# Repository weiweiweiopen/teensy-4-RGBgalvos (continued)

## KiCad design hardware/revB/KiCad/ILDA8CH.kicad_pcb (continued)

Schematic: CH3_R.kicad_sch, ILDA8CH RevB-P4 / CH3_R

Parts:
C161, C162: 4.7n; Capacitor_SMD__C_0603_1608Metric; MPN GRM1885C1H472JA01D; LCSC C85980
C163, C164: 100n; Capacitor_SMD__C_0603_1608Metric; MPN GRM188R71H104KA93D; LCSC C77055
C165, C166: 4.7u; Capacitor_SMD__C_0805_2012Metric; MPN GRM21BR61E475KA12L; LCSC C77077
R161, R162: 1k; Resistor_SMD__R_0603_1608Metric; MPN RT0603BRD071KL; LCSC C110776
R163, R164, R165, R166: 20k; Resistor_SMD__R_0603_1608Metric; MPN RT0603BRD0720KL; LCSC C723637
R167, R168: 10k; Resistor_SMD__R_0603_1608Metric; MPN RT0603BRD0710KL; LCSC C95204
R169, R170: 100k; Resistor_SMD__R_0603_1608Metric; MPN RC0603FR-07100KL; LCSC C14675
R405, R406: 10M; Resistor_SMD__R_0603_1608Metric; MPN RC0603FR-0710ML; LCSC C114606
U13: OPA4197IDR; Package_SO__SOIC-14_3.9x8.7mm_P1.27mm; MPN OPA4197IDR; LCSC C2058532

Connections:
+15A: C163.1, C165.1, U13.4 (V+); also elsewhere on the board
-15A: C164.2, C166.2, U13.11 (V-); also elsewhere on the board
B3N: R162.1, U13.6 (-), U13.7 (OUT)
B3P: R161.1, U13.1 (OUT), U13.2 (-)
F3N: C162.1, R162.2, R165.1
F3P: C161.1, R161.2, R163.1
GND: C161.2, C162.2, C163.2, C164.1, C165.2, C166.1, R164.2, R405.2, R406.2, U13.12 (+); also elsewhere on the board
IN3N: R170.2, R406.1, U13.5 (+)
IN3P: R169.2, R405.1, U13.3 (+)
INV3: R167.2, R168.2, U13.13 (-)
ISO_DAC3_N: R170.1; also elsewhere on the board
ISO_DAC3_P: R169.1; also elsewhere on the board
R_DRV_N: R168.1, U13.14 (OUT); also elsewhere on the board
R_DRV_P: R166.1, R167.1, U13.8 (OUT); also elsewhere on the board
SUM3N: R165.2, R166.2, U13.9 (-)
SUM3P: R163.2, R164.1, U13.10 (+)

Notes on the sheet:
DC coupled. Physical pin numbers; net names are global and channel-unique.
X/Y DC gain = 39k/(20k+1k); colour gain = 20k/(20k+1k). Calibrate in firmware.
A/B: unity-gain input buffers. C: matched subtractor. D: complementary driver.

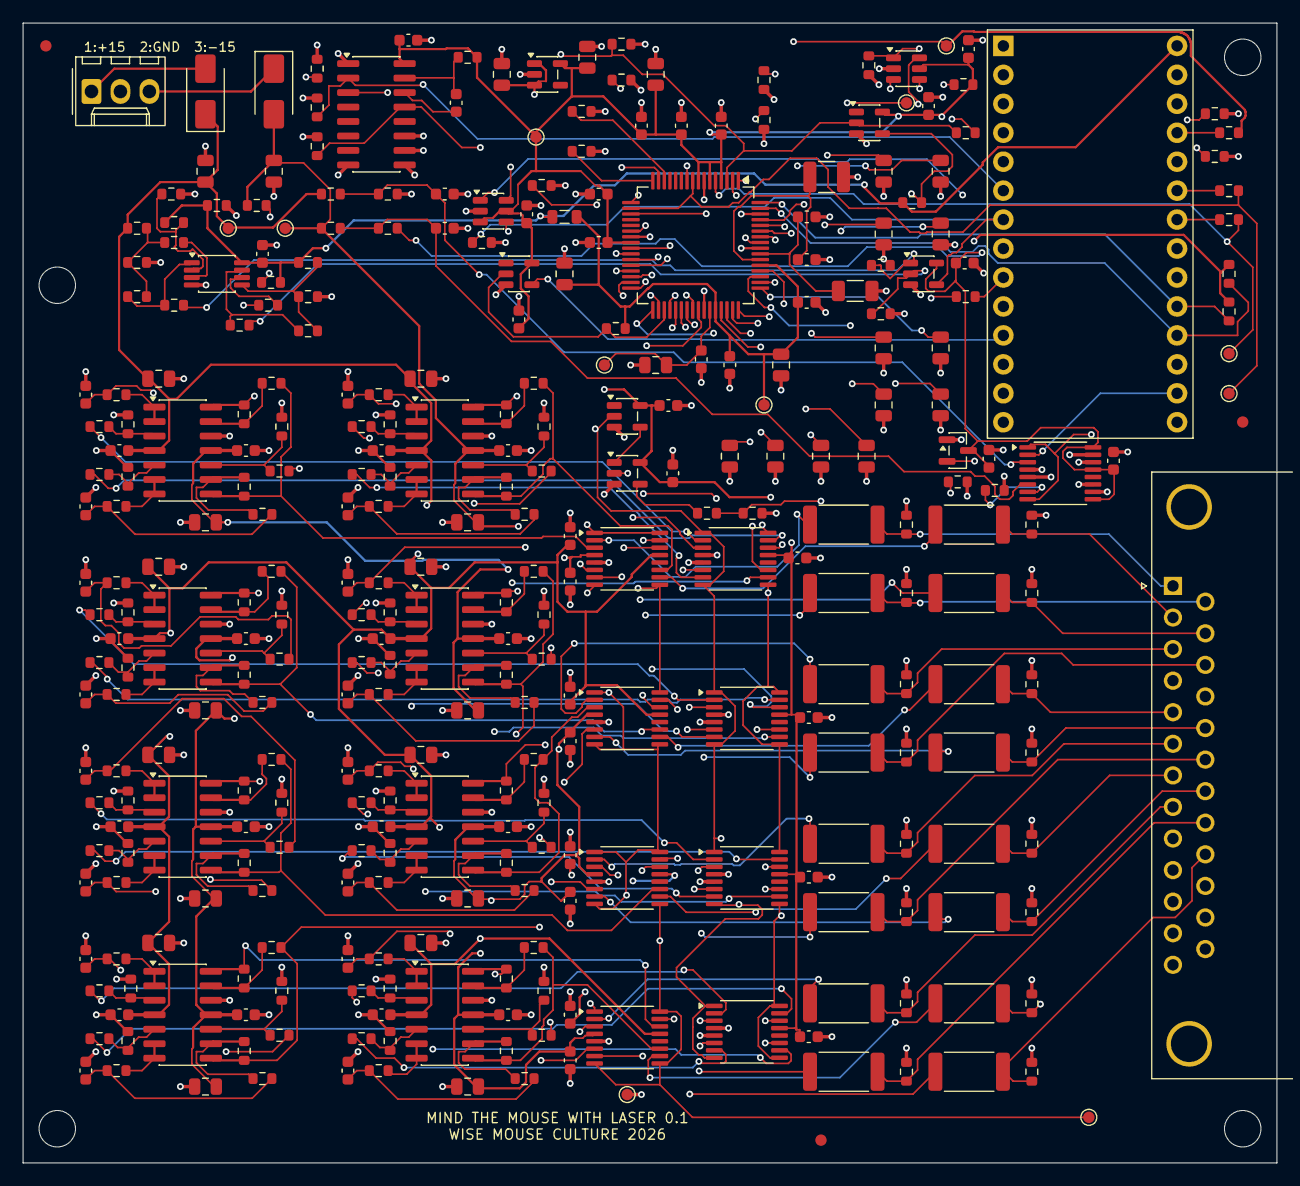
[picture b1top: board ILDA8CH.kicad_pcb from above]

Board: 4 copper layers, 110.0 x 100.0 mm, 337 parts (0 on the bottom side), 225 nets.

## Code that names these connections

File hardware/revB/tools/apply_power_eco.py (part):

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    assert len(original_refs) == 273
    # Preserve the already selected capacitor packages: change only which FILT
    # node each bulk capacitor serves, and subsequently reroute both nodes.
    pmap['C18']['pins']['1'] = 'FILT_ADC'
    pmap['C20']['pins']['1'] = 'FILT_DAC'
    pmap['A1']['pins']['26'] = 'MCU_3V3'
    pmap['A1']['pins']['7'] = 'RAILS_GOOD'
    pmap['A1']['pins']['16'] = 'ADC_P15'
    pmap['A1']['pins']['17'] = 'ADC_N15'
    pmap['R26']['pins']['2'] = 'MCU_3V3'
    pmap['R5']['pins']['1'] = 'RESET_QUALIFIED'
    pmap['U4']['pins']['3'] = 'ARM_QUALIFIED'
    pmap['U5']['pins']['1'] = 'DAC_ISOLATE_N'
    new = []
    def add(ref, value, pins, package, mpn, page, xy, angle=0, names=None):
        library, item = package.split(':', 1)
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    add('U6', 'TLV1702AIDGKR', {1:'RAILS_GOOD',2:'PREF',3:'PMON',4:'GND',5:'NREF',6:'NMON',7:'RAILS_GOOD',8:'USB_5V'},
        'Package_SO:VSSOP-8_3x3mm_P0.65mm', 'TLV1702AIDGKR', 'Power', [17,22],
        names={1:'OUT1',2:'IN1-',3:'IN1+',4:'GND',5:'IN2+',6:'IN2-',7:'OUT2',8:'VCC'})
    for ref, a, b, out, xy in [('U7','CODEC_RESET_GPIO','RAILS_GOOD','RESET_QUALIFIED',[77,6]),
                              ('U8','ARM','CODEC_RESET','ARM_QUALIFIED',[38,16])]:
        add(ref, 'SN74LVC1G08DBVR', {1:a,2:b,3:'GND',4:out,5:'+3V3'}, SOT,
            'SN74LVC1G08DBVR', 'Control', xy, names={1:'A',2:'B',3:'GND',4:'Y',5:'VCC'})
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        'Package_TO_SOT_SMD:SOT-23','TPS3839K33DBZR','Control',[96,7],
        names={1:'GND',2:'RESET_N',3:'VDD'})
    for row in range(4):
        pins={1:'CODEC_RESET',16:'DAC_ISOLATE_N',9:'DAC_ISOLATE_N',8:'CODEC_RESET',
              13:'USB_5V',4:'GND',5:'GND',12:None}
        for (s,d),(ch,leg) in zip([(3,2),(14,15),(11,10),(6,7)],
            [(2*row+1,'P'),(2*row+1,'N'),(2*row+2,'P'),(2*row+2,'N')]):
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
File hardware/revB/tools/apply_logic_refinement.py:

"""Resolve the reviewed comparator-LOW and CMOS-input-slew issues in the ECO.

KiCad Python; working copy only. Push-pull comparator outputs are never joined.
"""
from pathlib import Path
import copy
import json
import subprocess
import uuid
import pcbnew as k

ROOT=Path(__file__).resolve().parents[1];RUN=ROOT/'eco/power-sequencing-20261025';WORK=RUN/'project'
CLI='/Applications/KiCad/KiCad.app/Contents/MacOS/kicad-cli'
SYS=Path('/Applications/KiCad/KiCad.app/Contents/SharedSupport/footprints')
NS=uuid.UUID('fa12ee52-6575-495a-b639-073316e21250')
def uid(s):return str(uuid.uuid5(NS,s))
def v(x,y):return k.VECTOR2I(k.FromMM(x),k.FromMM(y))
def dump(p,d):p.write_text(json.dumps(d,indent=2)+'\n')

def main():
    assert not (RUN/'analysis/logic-refinement.json').exists()
    data=json.loads((WORK/'sources/electrical.json').read_text());parts=data['parts'];pmap={p['ref']:p for p in parts}
    pos=json.loads((WORK/'placement.json').read_text());queries=json.loads((RUN/'analysis/parts-search.json').read_text())['queries']
    board=k.LoadBoard(str(WORK/'KiCad/ILDA8CH.kicad_pcb'))
    def set_mpn(part,mpn,family):
        part.update(mpn=mpn,value=mpn,ds='https://www.ti.com/lit/ds/symlink/'+family.lower()+'.pdf')
        part['code']=next(r['componentCode'] for r in queries[mpn]['exact'] if (r.get('stockCount') or 0)>0)
    set_mpn(pmap['U6'],'TLV3202AIDGKR','TLV3202')
    pmap['U6']['pins'].update({'1':'RAIL_P_RAW','7':'RAIL_N_RAW'})
    pmap['U6']['pin_types'].update({'1':'output','7':'output'})
    set_mpn(pmap['U7'],'SN74LVC1G11DBVR','SN74LVC1G11')
    pmap['U7'].update(fp='ILDA8CH:Package_TO_SOT_SMD__SOT-23-6',source_fp='Package_TO_SOT_SMD:SOT-23-6',
        pins={'1':'CODEC_RESET_GPIO','2':'GND','3':'RAIL_P_GOOD','4':'RESET_QUALIFIED','5':'+3V3','6':'RAIL_N_GOOD'},
        pin_names={'1':'A','2':'GND','3':'B','4':'Y','5':'VCC','6':'C'},
        pin_types={'1':'input','2':'power_in','3':'input','4':'output','5':'power_in','6':'input'})
    pmap['R355']['pins']['1']='RAIL_P_RAW';pmap['R361']['pins']['1']='RAIL_N_RAW'
    pmap['R362']['pins']={'1':'RAILS_GOOD','2':'GND'}
    pmap['U5']['pins']['1']='SHUTTER_DISABLE'
    new=[]
    def clone(ref,template,pins,xy,page=None):
        part=copy.deepcopy(pmap[template]);part.update(ref=ref,uuid=uid(ref),pins=pins,xy=xy,angle=0)
        if page:part['page']=page
        parts.append(part);pmap[ref]=part;new.append(ref);pos['parts'][ref]=dict(xy=xy,angle=0)
        return part
    clone('U36','U8',{'1':'RAIL_P_GOOD','2':'RAIL_N_GOOD','3':'GND','4':'RAILS_GOOD','5':'MCU_3V3'},[81,20])
    part=clone('U37','U9',{'1':None,'2':'CODEC_RESET','3':'GND','4':'SHUTTER_DISABLE','5':'USB_5V'},[53,34.5])
    set_mpn(part,'SN74AHCT1G14DBVR','SN74AHCT1G14');part['pin_names']['4']='Y';part['pin_types']['4']='output'
    clone('C360','C350',{'1':'MCU_3V3','2':'GND'},[82,22],'Control')
    clone('C361','C350',{'1':'USB_5V','2':'GND'},[56,34.5],'Control')
    clone('R369','R352',{'1':'RAIL_P_GOOD','2':'GND'},[12.3,25.5],'Power')
    clone('R370','R352',{'1':'RAIL_N_GOOD','2':'GND'},[22,26.5],'Power')
    clone('R371','R1',{'1':'RAIL_P_RAW','2':'RAIL_P_GOOD'},[12.3,22.9],'Power')
    clone('R372','R1',{'1':'RAIL_N_RAW','2':'RAIL_N_GOOD'},[22,19.5],'Power')
    lib=WORK/'KiCad/ILDA8CH.pretty'
    fp=k.FootprintLoad(str(SYS/'Package_TO_SOT_SMD.pretty'),'SOT-23-6');assert fp
    fp.SetFPID(k.LIB_ID('ILDA8CH','Package_TO_SOT_SMD__SOT-23-6'))
    k.PCB_IO_MGR.FindPlugin(k.PCB_IO_MGR.KICAD_SEXP).FootprintSave(str(lib),fp)
    dump(WORK/'sources/electrical.json',data);dump(WORK/'placement.json',pos)
    script=WORK/'tools/design.py';script.write_text(script.read_text().replace('assert len(parts)==328','assert len(parts)==336'))
    subprocess.run([__import__('sys').executable,'-B',str(WORK/'tools/generate_schematic.py')],check=True)
    subprocess.run([CLI,'sch','export','netlist','--format','kicadxml','-o',str(WORK/'QA/native.net.xml'),str(WORK/'KiCad/ILDA8CH.kicad_sch')],check=True)
    import xml.etree.ElementTree as ET
    xml=ET.parse(WORK/'QA/native.net.xml').getroot();comps={c.get('ref'):c for c in xml.findall('components/comp')}
    nets={(n.get('ref'),n.get('pin')):net.get('name') for net in xml.findall('nets/net') for n in net.findall('node')}
    for name in set(nets.values()):
        if not board.FindNet(name):board.Add(k.NETINFO_ITEM(board,name,board.GetNetCount()))
    changed=[];old_u7=None
    for f in list(board.GetFootprints()):
        ref=f.GetReference()
        if ref=='U7':old_u7=f;board.Remove(f);continue
        part=pmap[ref];f.SetValue(part['value'])
        for field,key in [('MPN','mpn'),('LCSC','code'),('Datasheet','ds')]:f.SetField(field,part[key]);f.GetField(field).SetVisible(False)
        for pad in f.Pads():
            if not pad.GetNumber():continue
            name=nets[ref,pad.GetNumber()]
            if name!=pad.GetNetname():
                changed.append((pad.GetPosition(),pad.GetNetname()));pad.SetNet(board.FindNet(name))
    for ref in ['U7']+new:
        part=pmap[ref];f=k.FootprintLoad(str(lib),part['fp'].split(':',1)[1]);assert f
        f.SetReference(ref);f.SetValue(part['value']);f.SetFPID(k.LIB_ID(*part['fp'].split(':',1)));f.SetAttributes(k.FP_SMD)
        f.SetPosition(v(*pos['parts'][ref]['xy']));f.SetOrientationDegrees(pos['parts'][ref]['angle'])
        c=comps[ref];f.SetPath(k.KIID_PATH(c.find('sheetpath').get('tstamps').rstrip('/')+'/'+c.find('tstamps').text.split()[0]));f.SetSheetname('/'+part['page']+'/');f.SetSheetfile(part['page']+'.kicad_sch')
        for field,key in [('MPN','mpn'),('LCSC','code'),('Datasheet','ds')]:f.SetField(field,part[key]);f.GetField(field).SetVisible(False)
        f.SetField('Assembly','JLC SMT');f.GetField('Assembly').SetVisible(False)
        f.Reference().SetLayer(k.F_Fab);f.Reference().SetTextSize(v(.8,.8));f.Reference().SetTextThickness(k.FromMM(.12));f.Reference().SetVisible(True);f.Value().SetVisible(False)
        for pad in f.Pads():
            if pad.GetNumber():pad.SetNet(board.FindNet(nets[ref,pad.GetNumber()]))
        board.Add(f)
    for pad in old_u7.Pads():changed.append((pad.GetPosition(),pad.GetNetname()))
    removed=[]
    for t in list(board.GetTracks()):
        remove=t.GetNetname()=='RAILS_GOOD'
        if not isinstance(t,k.PCB_VIA):
            remove|=any(t.GetNetname()==name and (t.GetStart()==point or t.GetEnd()==point) for point,name in changed)
        if remove:removed.append(t);board.Remove(t)
    board.BuildConnectivity();k.ZONE_FILLER(board).Fill(board.Zones());assert k.SaveBoard(str(WORK/'KiCad/ILDA8CH.kicad_pcb'),board,True)
    dump(RUN/'analysis/logic-refinement.json',dict(new_refs=new,changed_ic=['U6','U7'],
        rationale='Push-pull separate comparator outputs; 3-input reset qualification; MCU-domain AND telemetry; independent Schmitt shutter-OE inverter.',
        old_open_collector_comparator_removed=True,parts=len(parts),removed_copper=len(removed)))
    print('Logic refinement applied:',len(parts),'parts')


if __name__=='__main__':main()

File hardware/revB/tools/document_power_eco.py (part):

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
USB5→U2→carrier3V3供codec VD／介面與watchdog；USB5→FB1→5VA供codec VA。Teensy自己的3V3經A1.26成為**MCU_3V3**，與carrier3V3分開。J2.1／.2／.3仍為+15／GND／−15，經D1/D2成為±15A。

硬體雙軌UV偵測不經100nF ADC濾波。兩個推挽good訊號經100Ω各自到U7及U36；GPIO5讀的是MCU供電的U36輸出。CODEC_RESET低時，DAC輸入隔離、U8 clear、U4 clear及SHUTTER OE共同禁止輸出。資料／時鐘／軟體電源窗口仍由韌體資格化。

新4.7k ADC bleed降低telemetry span，保留約22／26mV每12-bit LSB的rail解析度。MCU3V3的330Ωbleed約10mA／33mW；ARM、HEART及reset request各2.2k，下拉輸入HIGH約1.5mA，避免把原buffer後的下拉誤當作GPIO request下拉。

U2以約65mA估算0.111W；32個OPA amplifier quiescent約32mA typical、48mA max over-temperature的rail-through current，另加輸出負載。Analyzer generic電流估算未當作完整USB budget。USB removal、供電ramp及外部負載仍需波形資格化。

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
## Bus Topology / Firmware

GPIO2=reset request／active shutdown，4=heartbeat，5=hardware rail status，6=ARM fresh-edge clock，14/15=isolated ADC。U8是latch，**ARM LOW本身不再是立即clear**；新版韌體active disconnect同時拉RESET低並令codec重新初始化。硬體掉電、量測UV/OV與clock fault清除manual request；單純stream暫停保留既有enable request，可在重新初始化／stream恢復後重新觸發。

Wire1仍100kHz；八路USB／TDM mapping保留。RevB韌體已成功編譯且未燒錄。factory gain仍是降低範圍設定，需實板校準，不宣稱已達完整ILDA DC精度。

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
## Test Coverage

11個TP保留：GND、3V3、5VA、±15A、RUN、MCLK/LRCLK/BCLK/TDM、VQ。新增GPIO status可經R362量測；RESET/SCL/SDA無新專用TP。測試點百分比不是功能覆蓋率。實板仍需核對GPIO／codec init、positive/negative-only power、USB removal、reset、stuck heartbeat、負載、校準及溫升。

## False Positives / Reviewer Overrides

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
- [KiCad工程](KiCad/ILDA8CH.kicad_pro)／[PCB](KiCad/ILDA8CH.kicad_pcb)
- [原生DRC](QA/routing-drc.json)／[ERC](QA/erc.json)／[完整一致性與局部路徑audit](QA/power-eco-audit.json)
- [RevB韌體](firmware/ilda8ch_revB/ilda8ch_revB.ino)：八路USB/TDM已編譯、未燒錄。GPIO5=status、GPIO6=fresh ARM；active stop同時assert codec RESET。
- [電氣模型與邏輯回歸](QA/power-eco-verification.json)
- 新版原生preview以`preview/power-eco-*`檔為準；舊P3擺件／桌面截圖是歷史。

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
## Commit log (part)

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2026-06-23 Initial public release
